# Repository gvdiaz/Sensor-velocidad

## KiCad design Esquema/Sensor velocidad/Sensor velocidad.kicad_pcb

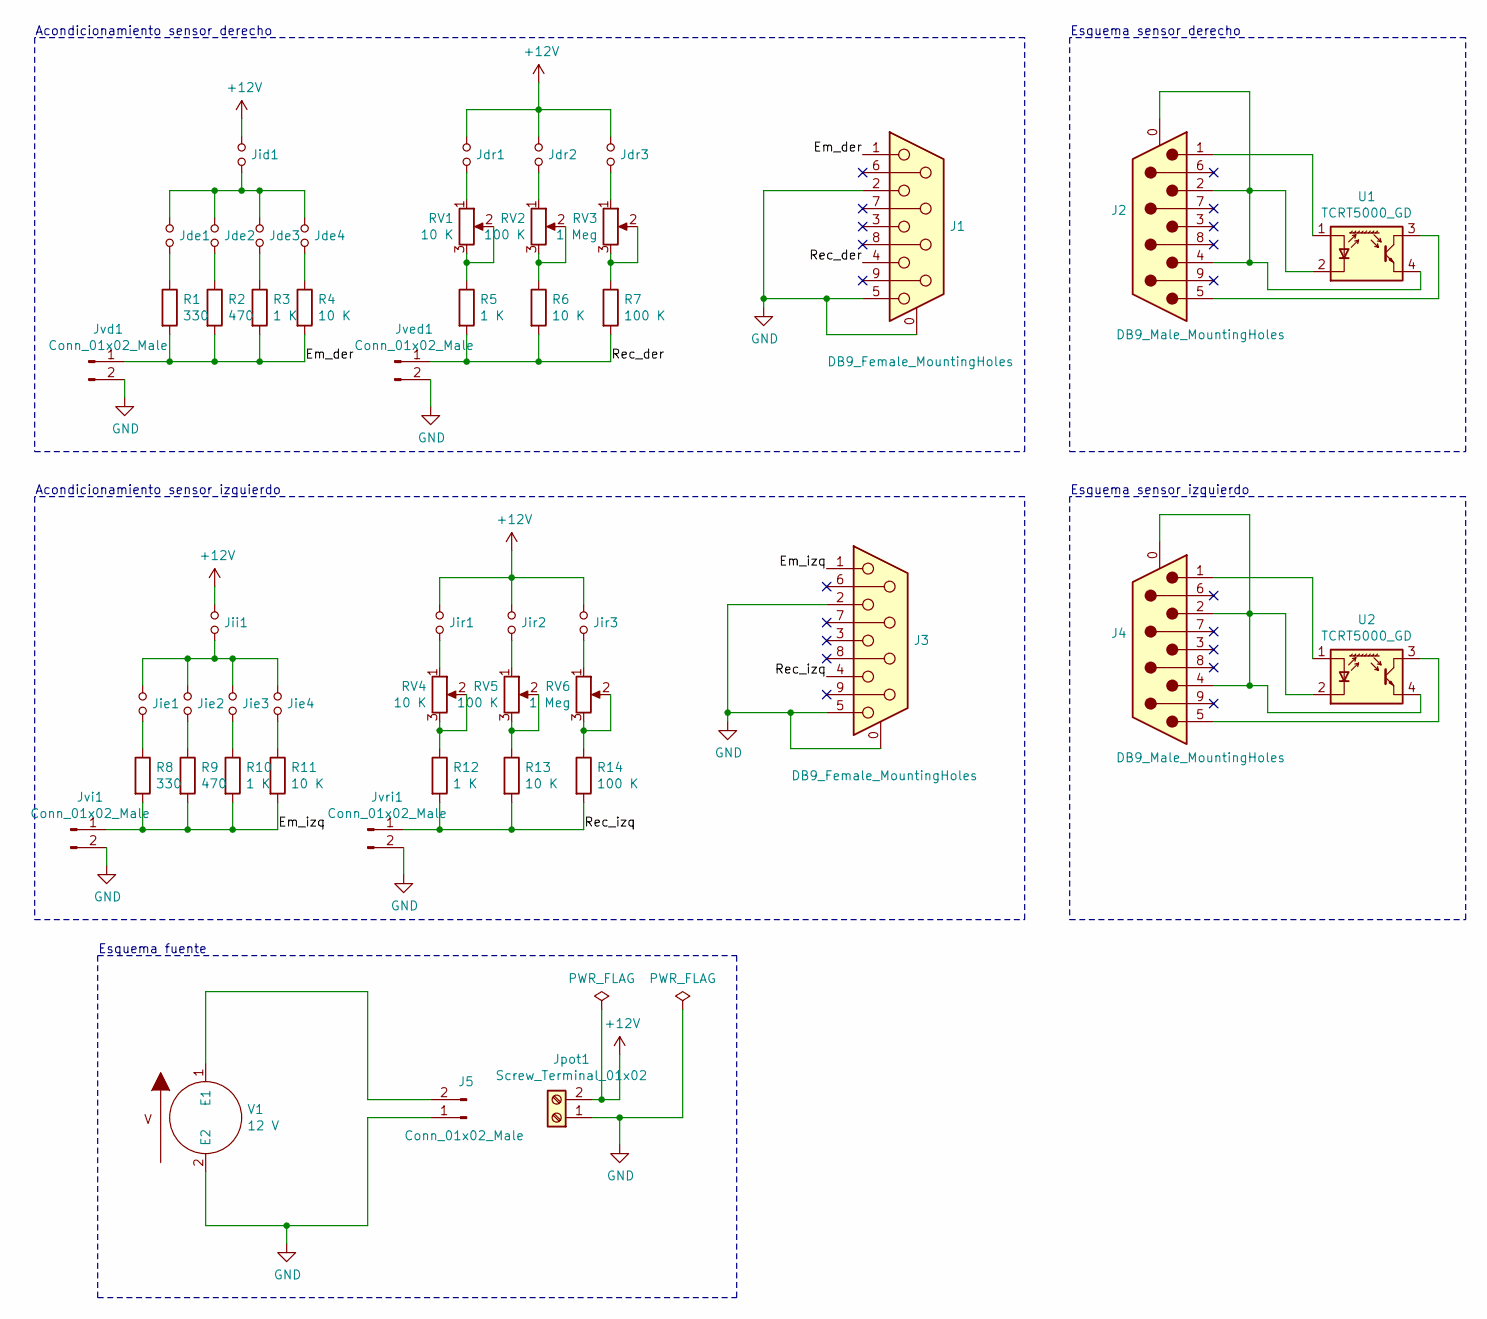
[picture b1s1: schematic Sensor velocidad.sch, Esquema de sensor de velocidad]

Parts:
J1, J3: DB9_Female_MountingHoles; DSUB-9_Female_Horizontal_P2.77x2.84mm_EdgePinOffset4.94mm_H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
J2, J4: DB9_Male_MountingHoles; DSUB-9_Male_Horizontal_P2.77x2.84mm_EdgePinOffset4.94mm_Hou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
J5: Conn_01x02_Male
Jde1, Jde2, Jde3, Jde4: Jumper_NO_Small; PinHeader_1x02_P1.27mm_Vertical
Jdr1, Jdr2, Jdr3: Jumper_NO_Small; PinHeader_1x02_P1.27mm_Vertical
Jid1: Jumper_NO_Small; PinHeader_1x02_P1.27mm_Vertical
Jie1, Jie2, Jie3, Jie4: Jumper_NO_Small; PinHeader_1x02_P1.27mm_Vertical
Jii1: Jumper_NO_Small; PinHeader_1x02_P1.27mm_Vertical
Jir1, Jir2, Jir3: Jumper_NO_Small; PinHeader_1x02_P1.27mm_Vertical
Jpot1: Screw_Terminal_01x02; TerminalBlock_bornier-2_P5.08mm
Jvd1: Conn_01x02_Male; PinHeader_1x02_P1.27mm_Vertical
Jved1: Conn_01x02_Male; PinHeader_1x02_P1.27mm_Vertical
Jvi1: Conn_01x02_Male; PinHeader_1x02_P1.27mm_Vertical
Jvri1: Conn_01x02_Male; PinHeader_1x02_P1.27mm_Vertical
R1, R8: 330; R_Axial_DIN0207_L6.3mm_D2.5mm_P7.62mm_Horizontal
R2, R9: 470; R_Axial_DIN0207_L6.3mm_D2.5mm_P7.62mm_Horizontal
R3, R5, R10, R12: 1 K; R_Axial_DIN0207_L6.3mm_D2.5mm_P7.62mm_Horizontal
R4, R6, R11, R13: 10 K; R_Axial_DIN0207_L6.3mm_D2.5mm_P7.62mm_Horizontal
R7, R14: 100 K; R_Axial_DIN0207_L6.3mm_D2.5mm_P7.62mm_Horizontal
RV1, RV4: 10 K; Potentiometer_Bourns_3299W_Vertical
RV2, RV5: 100 K; Potentiometer_Bourns_3299W_Vertical
RV3, RV6: 1 Meg; Potentiometer_Bourns_3299W_Vertical
U1, U2: TCRT5000_GD; TCRT5000
V1: 12 V

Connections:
+12V: Jdr1.1, Jdr2.1, Jdr3.1, Jid1.1, Jii1.1, Jir1.1, Jir2.1, Jir3.1, Jpot1.2
/Em_der: J1.1, Jvd1.1, R1.2, R2.2, R3.2, R4.2
/Em_izq: J3.1, Jvi1.1, R8.2, R9.2, R10.2, R11.2
/Rec_der: J1.4, Jved1.1, R5.2, R6.2, R7.2
/Rec_izq: J3.4, Jvri1.1, R12.2, R13.2, R14.2
GND: J1.0 (PAD), J1.2, J1.5, J3.0 (PAD), J3.2, J3.5, J5.1, Jpot1.1, Jvd1.2, Jved1.2, Jvi1.2, Jvri1.2, V1.2 (E2)
unnamed: J2.0 (PAD), J2.2, J2.4, U1.2 (K), U1.4 (E)
unnamed: J2.1, U1.1 (A)
unnamed: J2.5, U1.3 (C)
unnamed: J4.0 (PAD), J4.2, J4.4, U2.2 (K), U2.4 (E)
unnamed: J4.1, U2.1 (A)
unnamed: J4.5, U2.3 (C)
unnamed: J5.2, V1.1 (E1)
unnamed: Jde1.1, Jde2.1, Jde3.1, Jde4.1, Jid1.2
unnamed: Jde1.2, R1.1
unnamed: Jde2.2, R2.1
unnamed: Jde3.2, R3.1
unnamed: Jde4.2, R4.1
unnamed: Jdr1.2, RV1.1
unnamed: Jdr2.2, RV2.1
unnamed: Jdr3.2, RV3.1
unnamed: Jie1.1, Jie2.1, Jie3.1, Jie4.1, Jii1.2
unnamed: Jie1.2, R8.1
unnamed: Jie2.2, R9.1
unnamed: Jie3.2, R10.1
unnamed: Jie4.2, R11.1
unnamed: Jir1.2, RV4.1
unnamed: Jir2.2, RV5.1
unnamed: Jir3.2, RV6.1
unnamed: R5.1, RV1.2, RV1.3
unnamed: R6.1, RV2.2, RV2.3
unnamed: R7.1, RV3.2, RV3.3
unnamed: R12.1, RV4.2, RV4.3
unnamed: R13.1, RV5.2, RV5.3
unnamed: R14.1, RV6.2, RV6.3

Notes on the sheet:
Acondicionamiento sensor derecho
Acondicionamiento sensor izquierdo
Esquema sensor derecho
Esquema sensor izquierdo
Esquema fuente

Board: 2 copper layers, 47 parts (0 on the bottom side), 34 nets, no tracks yet.

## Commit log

2019-09-24 Documento de inicio para definir el circuito que mide la velocidad de rotor
2019-09-24 Esquema para definir circuito de sensor de velocidad
2019-09-25 Documento que comenta la detención de la implementación del desarrollo del sensor de velocidad
2020-05-14 Agrego archivo de git ignore para los archivos temporales de libre office
2020-05-14 Agrego versiones de informes en XML para poder aplicar la diferenciación cuando subo alguna versión.
2020-05-14 Quito version vieja de los archivos en formato odt
2020-05-14 Agrego requerimientos de PCB.
2020-05-14 Coloco componentes en esquema.
2020-05-15 Agregué requerimientos de medir los dos sensores y puntos de medición
2020-05-15 Avance sobre esquemático, agregué sensores y conectores
2020-05-16 Agregué a la tabla de archivos ignorados los autosalvados de libreoffice
2020-05-16 Agregué requerimiento de medición de corriente en placa
2020-05-16 Agregué componentes y a los componentes sus funciones (a la mayoría)
2020-05-16 Modifiqué error en puntos de medición de diodo y nomenclatura jumpers para sensor izquierdo y derecho
2020-05-16 Corregí nomenclatura de jumper de medición de receptor
2020-05-16 Acomodé espacialmente el circuito esquemático
2020-05-16 Primera versión de esquemático para sensado de desbalanceo en ambos lados
2020-05-16 Esquema con función annotate ejecutada
2020-05-16 Agregué labels de power port a la alimentación +12V y GND como recomendó la función ERC
2020-05-16 Empecé a agregar footprints a los componentes
2020-05-16 Acomodé requerimientos
2020-05-17 Registro de nuevo branch y su objetivo
2020-05-17 Intenté agregar a git ignore el archivo fp-info-cache pero no pude, debo seguir intentando
2020-05-17 Agregué footprints a casi todos los componentes, me queda el TCRT5000 el cual hay un footprint en un repo de github
2020-05-18 Agrego la resolución de la incertidumbre asumida en la rama config_1
2020-05-18 Modifiqué el archivo para que evite mostrar el archivo fp-info-cache, finalmente funcionó
2020-05-18 Agrego primer versión de footprint TCRT5000
2020-05-19 Modifiqué el footprint agregando coutyard y otras pequeñas cosas
2020-05-19 Agregué a la biblioteca de footprint el pinheader agrandando el ancho de pads
2020-05-19 Reasigné el footprint modificado a los jumpers
2020-05-20 Agregué requerimiento sobre filtro de entrada
2020-05-21 Cálculo y diseño de filtro de entrada
2020-05-21 Agregué curva de módulo en cálculo de circuito pi.
2020-05-24 primer versión de filtro para circuitosd
2020-05-25 Simulación de filtro pi antes de agregar la comparación con el filtro T
2020-05-27 quité archivos llamado Draft
2020-05-27 Simulación de filtro T
2020-05-27 Cambio de nombre de simulación de filtro
2020-05-27 Archivos para comparación de simulación con cálculo de impedancia de entrada
2020-05-27 Agregué puntos de cálculo hasta 1 kHz para compararlo con simulación
2020-05-28 Pasé el cálculo a xml para poder verlo en el diff.
2020-05-28 Saqué las simulaciones que estaban sin nombre definido y lo reemplazo por Filtro_T.
2020-05-28 Archivos de simulación.
2020-05-28 Archivos de salida para realizar la comparación entre cálculo y simulación de filtro.
2020-05-28 Agregué información de procesamiento para las dos simulaciones.
2020-05-28 Versión de archivo con comparación de filtro pi y T.
2020-05-28 Borrado de filtro de archivos .net de simulaciones.
2020-05-29 Modificación de lineas de trazo para gráficos de cálculos y de simulación
2020-05-29 Documento de conclusión de filtro pasabajos
2020-05-29 Agrego el cálculo de impedancia de compleja de cada filtro en vez de solo el módulo.
2020-05-30 Cálculo y simulación finalmente comparadas.
2020-05-31 Avance de documento de filtro
2020-05-31 Modificación en título de gráficos para exportarlos a informe.
2020-05-31 Gráficos para ser utilizados en informe.
2020-05-31 Primera versión de informe de análisis de filtros.
2020-05-31 Seteo de page set-up en board
2020-05-31 Archivo de placa
2020-05-31 Agrego el componente de sensado de distancia
2020-05-31 Seteo de cantidad de capas (2) para placas de sensores y dibujado de separación mínima de tornillería de sensor infrarojo
2020-05-31 Modificación de distancia mínima entre tornillos de sujección y revisé las design rules
2020-05-31 Generación de net file para levantarlo en programa de PCB
2020-05-31 Agregué componentes a proyecto pcb
2020-05-31 Agregué a biblioteca componentes conectores DB con conector de masa diseñado a medida, resta cargarlos en .net
2020-05-31 Modificación de footprints en conectores db para que se vea reflejado en pcb
2020-05-31 Voy acomodando los componentes de la placa, modificar footprint de jumpers porque tienen muy grande los pads
2020-05-31 Agregué requerimiento de tamaño mínimo de pcb de sensor, falta ingresar imagen
2020-06-01 Cambio en tamaño de pad para que no tenga problema con las reglas de ruteo.
2020-06-01 Modificación de componentes en placa según el nuevo footprint
2020-06-01 Acomodé los componentes de las placas de sensado derecho.
2020-06-03 Terminé de acomodar a grandes rasgos los componentes
2020-06-03 Avance de placa, queda acomodar puntos de medición
2020-06-04 Cambié nombre de archivo a planificación ensayo
2020-06-04 Avance de planificación de ensayo
2020-06-20 Dejo registro de los racionales bajo los cuales planifico los ensayos sobre el sensor de posición
2020-06-20 Modificación pequeña a documento
2020-06-21 Script para ejemplo de manejo de archivos necesario para ensayo
2020-06-22 Modificación de código. Pude utilizar las funciones de fecha y hora y pude dirigir directorios.
2020-06-22 Archivo de salida que genera el código.
2021-03-14 Diagrama de bloques de ensayo de desbalanceo
2021-04-03 Agrego bibliografía de python para estudio
